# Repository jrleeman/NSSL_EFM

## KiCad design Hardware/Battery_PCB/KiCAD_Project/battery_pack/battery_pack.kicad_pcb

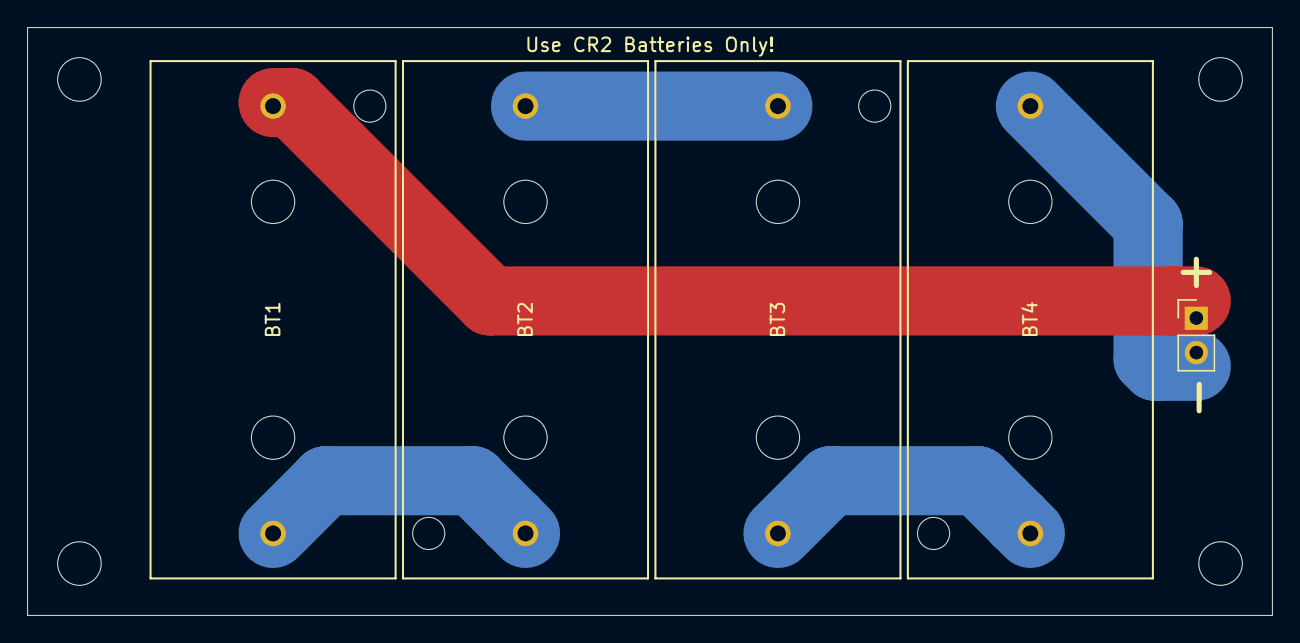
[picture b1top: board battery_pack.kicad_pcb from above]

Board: 2 copper layers, 91.4 x 43.2 mm, 9 parts (0 on the bottom side), 5 nets.

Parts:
BT1, BT2, BT3, BT4: CR2; BH-CR2-PC
H1, H2, H3, H4: MountingHole; MountingHole_3.2mm_M3_ISO7380
J1: Conn_01x02; Pin_Header_Straight_1x02_Pitch2.54mm

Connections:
unnamed: BT1.1, J1.1
unnamed: BT1.2, BT2.1
unnamed: BT2.2, BT3.1
unnamed: BT3.2, BT4.1
unnamed: BT4.2, J1.2
